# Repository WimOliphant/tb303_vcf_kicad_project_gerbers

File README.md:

# tb303_vcf_kicad_project_gerbers

UNTESTED UNTESTED! (known errata at bottom:)

This is the project files for the schematic and PCB layout in KiCad for the Roland TB303 VCF for 12v modular system. Schematic via Eddy Bergman:

https://www.eddybergman.com/2025/03/TB303-VCF.html

Thanks Eddy!

This project is my effort to add something back to the synth DIY community, and make use of pcb fabrication services.

It is for building a Voltage Controller Filter based on the Roland TB303 for -12/+12 modular systems.

Gerber zip is located in the "production" folder.

PLEASE NOTE: Currently this copy of the schematic and PCB is untested. Use at your own risk! (version 0.02 30/2/25)

KNOWN ERRATA:
 - C10, C11, C12, C13 (caps in the diode ladder between the transistors are labeled "uF", but they should be labelled "nF".

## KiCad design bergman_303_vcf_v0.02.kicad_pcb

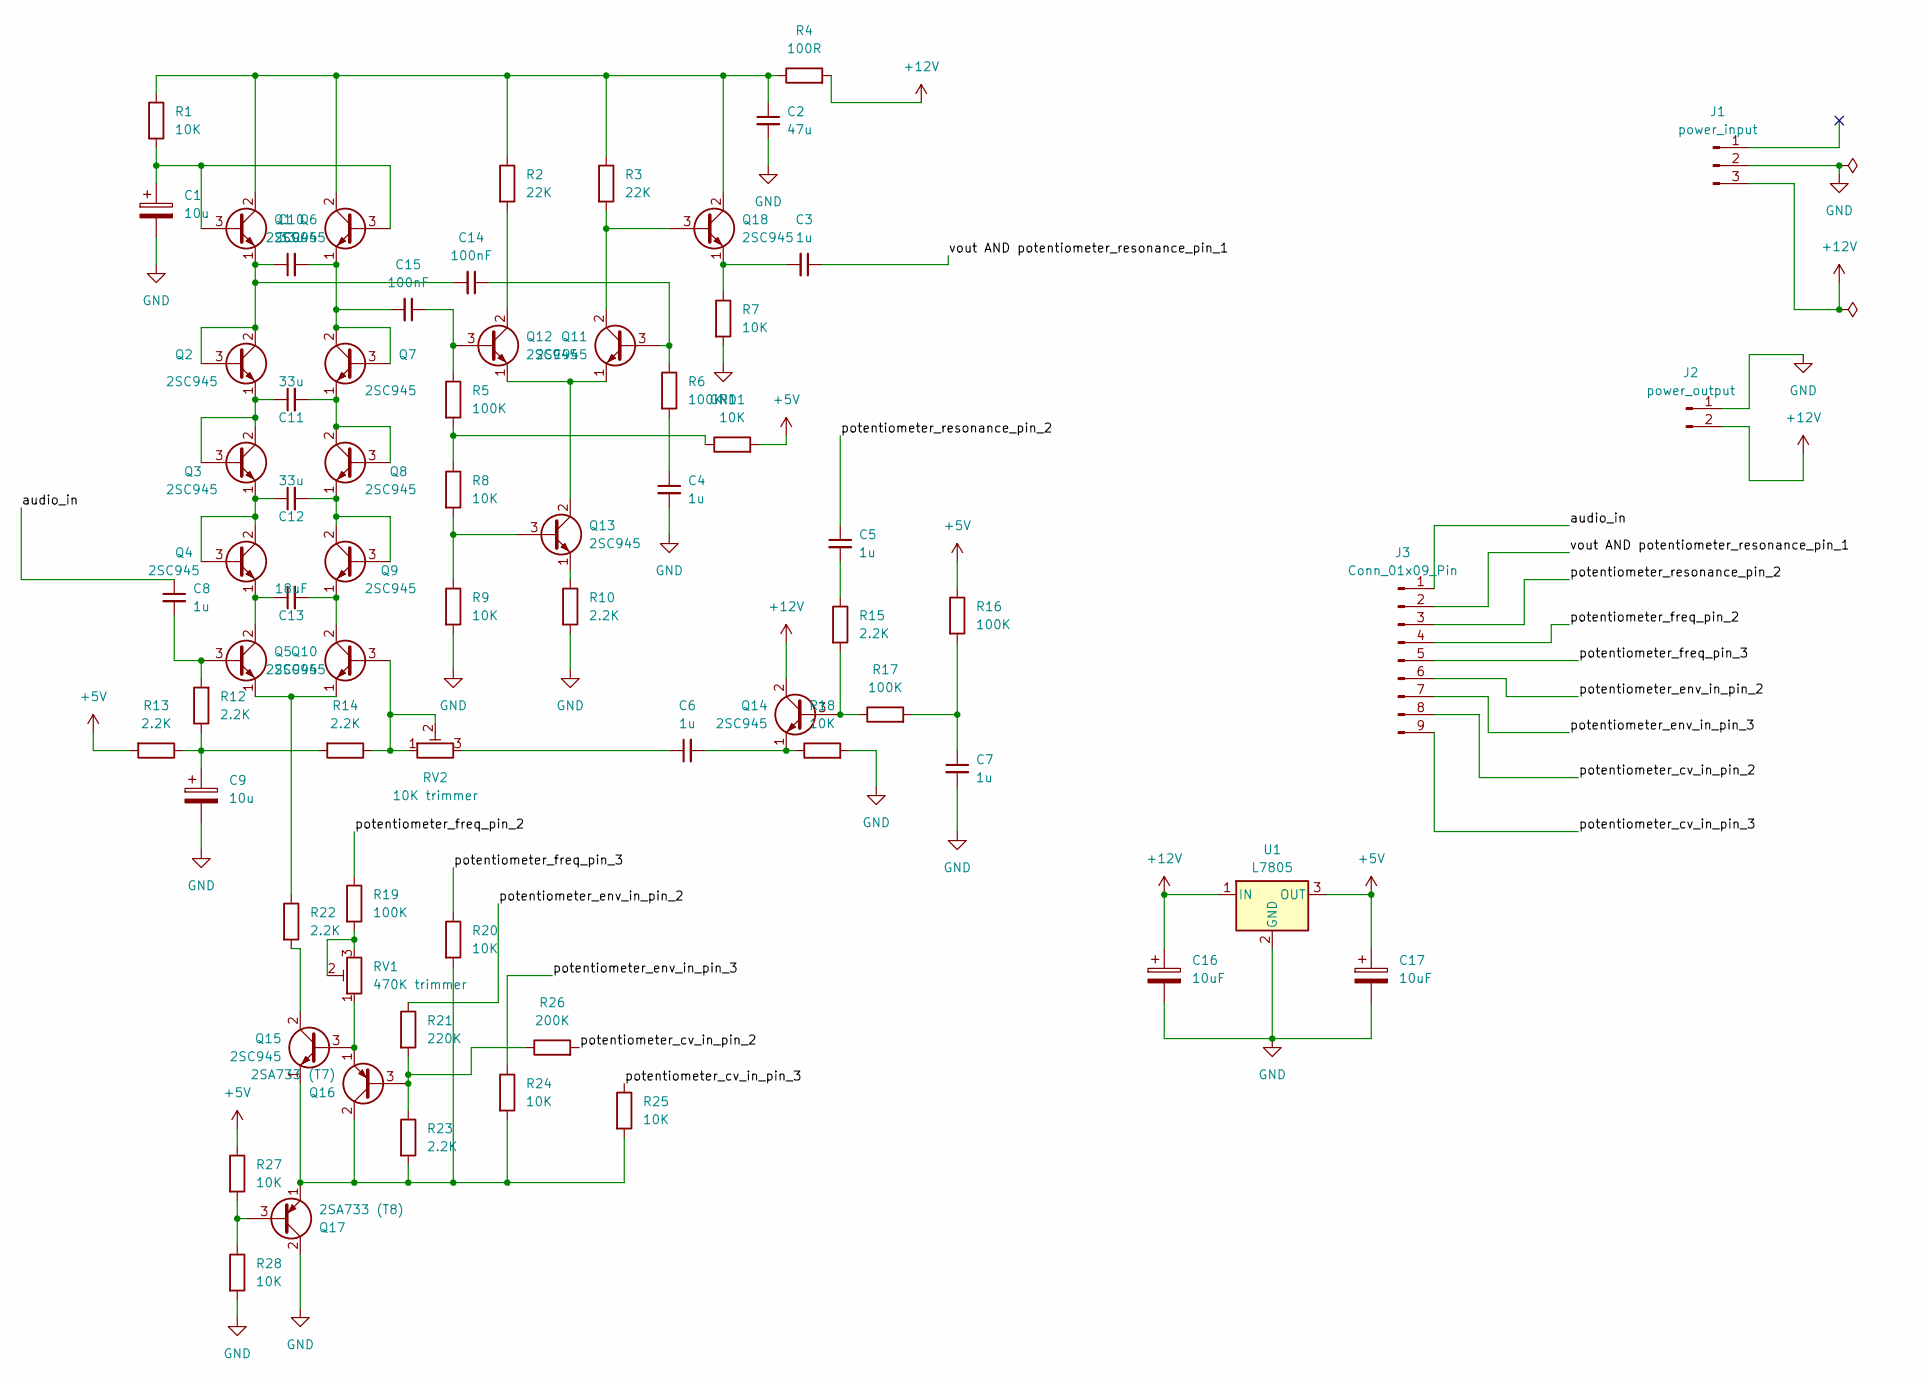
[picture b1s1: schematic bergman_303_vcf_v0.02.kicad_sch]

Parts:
C1, C9: 10u; CP_Radial_D6.3mm_P2.50mm
C2: 47u; C_Disc_D5.0mm_W2.5mm_P5.00mm
C3, C4, C5, C6, C7, C8: 1u; C_Disc_D5.0mm_W2.5mm_P5.00mm
C10, C11, C12: 33u; C_Disc_D7.5mm_W5.0mm_P7.50mm
C13: 18uF; C_Disc_D7.5mm_W5.0mm_P7.50mm
C14, C15: 100nF; C_Disc_D5.0mm_W2.5mm_P5.00mm
C16, C17: 10uF; CP_Radial_D6.3mm_P2.50mm
J1: power_input; Samtec_HPM-03-05-x-S_Straight_1x03_Pitch5.08mm
J2: power_output; PinHeader_1x02_P2.54mm_Vertical
J3: Conn_01x09_Pin; PinHeader_1x09_P2.54mm_Vertical
Q1, Q2, Q3, Q4, Q5, Q6, Q7, Q8, Q9, Q10, Q11, Q12, Q13, Q14, Q15, Q18: 2SC945; TO-92L_Inline_Wide
Q16: 2SA733 (T7); TO-92L_Inline_Wide
Q17: 2SA733 (T8); TO-92L_Inline_Wide
R1, R7, R8, R9, R11, R18, R20, R24, R25, R27, R28: 10K; R_Axial_DIN0204_L3.6mm_D1.6mm_P7.62mm_Horizontal
R2, R3: 22K; R_Axial_DIN0204_L3.6mm_D1.6mm_P7.62mm_Horizontal
R4: 100R; R_Axial_DIN0204_L3.6mm_D1.6mm_P7.62mm_Horizontal
R5, R6, R16, R17, R19: 100K; R_Axial_DIN0204_L3.6mm_D1.6mm_P7.62mm_Horizontal
R10, R12, R13, R14, R15, R22, R23: 2.2K; R_Axial_DIN0204_L3.6mm_D1.6mm_P7.62mm_Horizontal
R21: 220K; R_Axial_DIN0204_L3.6mm_D1.6mm_P7.62mm_Horizontal
R26: 200K; R_Axial_DIN0204_L3.6mm_D1.6mm_P7.62mm_Horizontal
RV1: 470K trimmer; Potentiometer_Bourns_3296W_Vertical
RV2: 10K trimmer; Potentiometer_Bourns_3296W_Vertical
U1: L7805; PinHeader_1x03_P2.54mm_Vertical

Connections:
+5V: C17.1, R11.2, R13.2, R16.1, R27.1, U1.3 (OUT)
+12V: C16.1, J1.3, J2.2, Q14.2 (C), R4.2, U1.1 (IN)
/audio_in: C8.1, J3.1
/potentiometer_cv_in_pin_2: J3.8, R26.2
/potentiometer_cv_in_pin_3: J3.9, R25.1
/potentiometer_env_in_pin_2: J3.6, R21.1
/potentiometer_env_in_pin_3: J3.7, R24.1
/potentiometer_freq_pin_2: J3.4, R19.1
/potentiometer_freq_pin_3: J3.5, R20.1
/potentiometer_resonance_pin_2: C5.1, J3.3
/vout AND potentiometer_resonance_pin_1: C3.1, J3.2
GND: C1.2, C2.2, C4.2, C7.2, C9.2, C16.2, C17.2, J1.2, J2.1, Q17.2 (C), R7.2, R9.2, R10.2, R18.2, R28.2, U1.2 (GND)
unnamed: C4.1, R6.2
unnamed: C5.2, R15.1
unnamed: C6.1, RV2.3
unnamed: C7.1, R16.2, R17.2
unnamed: C9.1, R12.1, R13.1, R14.2
unnamed: C1.1, Q1.3 (B), Q6.3 (B), R1.2
unnamed: C2.1, Q1.2 (C), Q6.2 (C), Q18.2 (C), R1.1, R2.1, R3.1, R4.1
unnamed: C10.1, C14.2, Q1.1 (E), Q2.2 (C), Q2.3 (B)
unnamed: C11.1, Q2.1 (E), Q3.2 (C), Q3.3 (B)
unnamed: C12.1, Q3.1 (E), Q4.2 (C), Q4.3 (B)
unnamed: C13.1, Q4.1 (E), Q5.2 (C)
unnamed: C8.2, Q5.3 (B), R12.2
unnamed: C10.2, C15.2, Q6.1 (E), Q7.2 (C), Q7.3 (B)
unnamed: C11.2, Q7.1 (E), Q8.2 (C), Q8.3 (B)
unnamed: C12.2, Q8.1 (E), Q9.2 (C), Q9.3 (B)
unnamed: Q10.3 (B), R14.1, RV2.1, RV2.2
unnamed: C13.2, Q9.1 (E), Q10.2 (C)
unnamed: Q5.1 (E), Q10.1 (E), R22.1
unnamed: C14.1, Q11.3 (B), R6.1
unnamed: Q11.2 (C), Q18.3 (B), R3.2
unnamed: Q11.1 (E), Q12.1 (E), Q13.2 (C)
unnamed: C15.1, Q12.3 (B), R5.1
unnamed: Q12.2 (C), R2.2
unnamed: Q13.3 (B), R8.2, R9.1
unnamed: Q13.1 (E), R10.1
unnamed: Q14.3 (B), R15.2, R17.1
unnamed: C6.2, Q14.1 (E), R18.1
unnamed: Q15.3 (B), Q16.1 (E), RV1.1
unnamed: Q15.2 (C), R22.2
unnamed: Q15.1 (E), Q16.2 (C), Q17.1 (E), R20.2, R23.2, R24.2, R25.2
unnamed: Q16.3 (B), R21.2, R23.1, R26.1
unnamed: Q17.3 (B), R27.2, R28.1
unnamed: C3.2, Q18.1 (E), R7.1
unnamed: R5.2, R8.1, R11.1
unnamed: R19.2, RV1.2, RV1.3

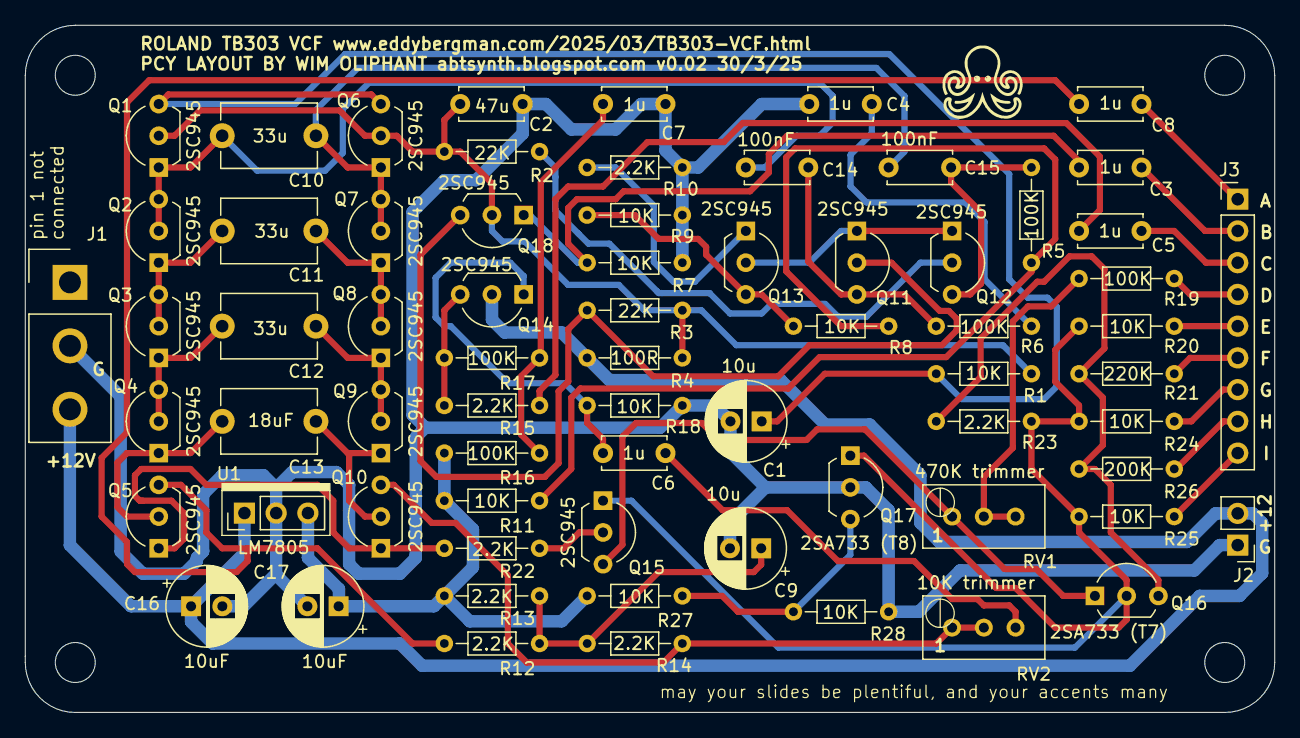
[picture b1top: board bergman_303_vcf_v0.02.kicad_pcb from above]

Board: 2 copper layers, 100.0 x 55.0 mm, 69 parts (0 on the bottom side), 47 nets.

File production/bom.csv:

Designator,Footprint,Quantity,Value,LCSC Part #
"C1, C9",CP_Radial_D6.3mm_P2.50mm,2,10u,
"C10, C11, C12",C_Disc_D7.5mm_W5.0mm_P7.50mm,3,33u,
C13,C_Disc_D7.5mm_W5.0mm_P7.50mm,1,18uF,
"C14, C15",C_Disc_D5.0mm_W2.5mm_P5.00mm,2,100nF,
"C16, C17",CP_Radial_D6.3mm_P2.50mm,2,10uF,
C2,C_Disc_D5.0mm_W2.5mm_P5.00mm,1,47u,
"C3, C4, C5, C6, C7, C8",C_Disc_D5.0mm_W2.5mm_P5.00mm,6,1u,
J1,Samtec_HPM-03-05-x-S_Straight_1x03_Pitch5.08mm,1,power_input,
J2,PinHeader_1x02_P2.54mm_Vertical,1,power_output,
J3,PinHeader_1x09_P2.54mm_Vertical,1,Conn_01x09_Pin,
"Q1, Q10, Q11, Q12, Q13, Q14, Q15, Q18, Q2, Q3, Q4, Q5, Q6, Q7, Q8, Q9",TO-92L_Inline_Wide,16,2SC945,
Q16,TO-92L_Inline_Wide,1,2SA733 (T7),
Q17,TO-92L_Inline_Wide,1,2SA733 (T8),
"R1, R11, R18, R20, R24, R25, R27, R28, R7, R8, R9",R_Axial_DIN0204_L3.6mm_D1.6mm_P7.62mm_Horizontal,11,10K,
"R10, R12, R13, R14, R15, R22, R23",R_Axial_DIN0204_L3.6mm_D1.6mm_P7.62mm_Horizontal,7,2.2K,
"R16, R17, R19, R5, R6",R_Axial_DIN0204_L3.6mm_D1.6mm_P7.62mm_Horizontal,5,100K,
"R2, R3",R_Axial_DIN0204_L3.6mm_D1.6mm_P7.62mm_Horizontal,2,22K,
R21,R_Axial_DIN0204_L3.6mm_D1.6mm_P7.62mm_Horizontal,1,220K,
R26,R_Axial_DIN0204_L3.6mm_D1.6mm_P7.62mm_Horizontal,1,200K,
R4,R_Axial_DIN0204_L3.6mm_D1.6mm_P7.62mm_Horizontal,1,100R,
RV1,Potentiometer_Bourns_3296W_Vertical,1,470K trimmer,
RV2,Potentiometer_Bourns_3296W_Vertical,1,10K trimmer,
U1,PinHeader_1x03_P2.54mm_Vertical,1,LM7805,

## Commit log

2025-03-31 Update README.md
    added errata re caps labels
